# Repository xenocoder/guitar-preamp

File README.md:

Version 1.0
Initial design, sent to OSHPark April 2014. Made for internal cavity of guitar

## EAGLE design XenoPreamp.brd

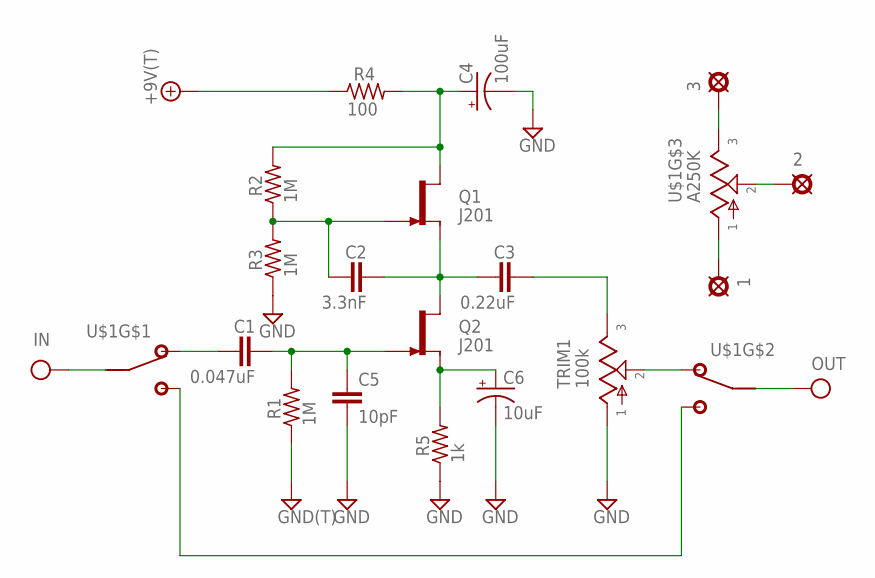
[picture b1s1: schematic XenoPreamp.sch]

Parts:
1: VOLIN; OCTOGON
2: VOLOUT; OCTOGON
3: GNF; OCTOGON
+9V: +9V(T); SQUARE
C1: 0.047uF; 072X025
C2: 3.3nF; 072X025
C3: 0.22uF; 072X025
C4: 100uF; 063_025
C5: 10pF; 050X030_025
C6: 10uF; 050_020_1
GND: GND(T); SQUARE
IN: IN(T); SQUARE
OUT: OUT(T); SQUARE
Q1, Q2: J201; TO92-
R1, R2, R3: 1M; R0207/3
R4: 100; R0207/3
R5: 1k; R0207/3
TRIM1: 100k; B25P
U$1: A250K; 16MM-PCB-MOUNT-DPDT

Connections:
+9V: +9V.1, R4.1
GND: C4.-, C5.2, C6.-, GND.1, R1.1, R3.1, R5.1, TRIM1.1
IN: IN.1, U$1.SA2 (2)
unnamed: C6.+, Q2.2 (S), R5.2
unnamed: C2.1, Q1.1 (G), R2.1, R3.2
unnamed: C4.+, Q1.3 (D), R2.2, R4.2
unnamed: C2.2, C3.1, Q1.2 (S), Q2.3 (D)
unnamed: C1.2, C5.1, Q2.1 (G), R1.2
unnamed: C3.2, TRIM1.3
unnamed: 3.1, U$1.3
unnamed: 2.1, U$1.2
unnamed: 1.1, U$1.1
unnamed: U$1.SA3 (3), U$1.SB3 (3)
unnamed: TRIM1.2, U$1.SB1 (1)
unnamed: C1.1, U$1.SA1 (1)
OUT: OUT.1, U$1.SB2 (2)

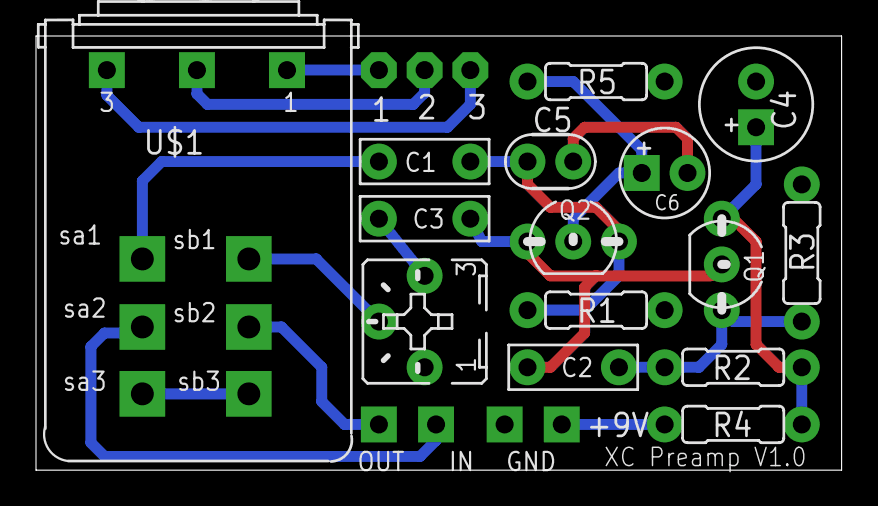
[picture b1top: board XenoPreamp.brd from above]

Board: 2 copper layers, 44.8 x 24.1 mm, 22 parts (0 on the bottom side), 16 nets.
